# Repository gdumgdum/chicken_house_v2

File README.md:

# chicken_house_v2
Everything needed to automate a chicken house door controlled over RF by domotic softwares

#

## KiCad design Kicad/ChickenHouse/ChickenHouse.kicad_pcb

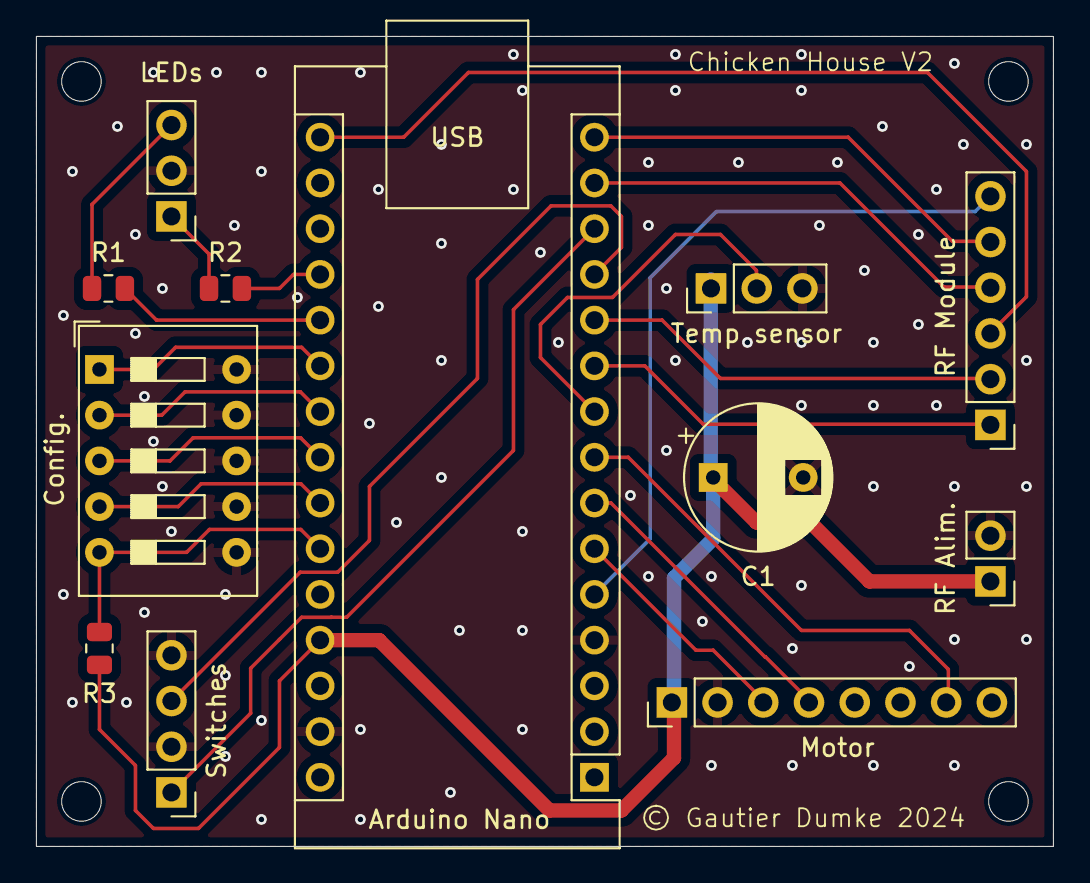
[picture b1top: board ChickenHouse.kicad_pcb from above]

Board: 2 copper layers, 56.5 x 45.0 mm, 12 parts (0 on the bottom side), 23 nets.

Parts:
Arduino Nano: Arduino_Nano_v3.x; Arduino_Nano
C1: 220µF/16V; CP_Radial_D8.0mm_P5.00mm
Config.: SW_DIP_x05; SW_DIP_SPSTx05_Slide_9.78x14.88mm_W7.62mm_P2.54mm
LEDs: LEDs; PinHeader_1x03_P2.54mm_Vertical
Motor: LM239D Shield; PinHeader_1x08_P2.54mm_Vertical
R1, R2, R3: 470; R_0805_2012Metric
RF Alim.: Conn_01x02; PinHeader_1x02_P2.54mm_Vertical
RF Module: Conn_01x06; PinHeader_1x06_P2.54mm_Vertical
Switches: Switches; PinHeader_1x04_P2.54mm_Vertical
Temp sensor: Temperature; PinHeader_1x03_P2.54mm_Vertical

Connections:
+5V: Arduino Nano.27 (+5V), C1.1, Motor.1, R3.1, RF Alim..1, Temp sensor.1
GND: Arduino Nano.4 (GND), Arduino Nano.29 (GND), C1.2, Config..6, Config..7, Config..8, Config..9, Config..10, LEDs.2, Motor.2, RF Alim..2, Switches.2, Switches.4, Temp sensor.3
unnamed: Arduino Nano.19 (A0), R2.2
unnamed: Arduino Nano.20 (A1), R1.2
unnamed: Arduino Nano.21 (A2), Config..1
unnamed: Arduino Nano.22 (A3), Config..2
unnamed: Arduino Nano.23 (A4), Config..3
unnamed: Arduino Nano.24 (A5), Config..4
unnamed: Arduino Nano.25 (A6), Config..5, R3.2
unnamed: Arduino Nano.5 (D2), RF Module.6
unnamed: Arduino Nano.6 (D3), Motor.3
unnamed: Arduino Nano.7 (D4), Motor.4
unnamed: Arduino Nano.8 (D5), Motor.7
unnamed: Arduino Nano.9 (D6), Temp sensor.2
unnamed: Arduino Nano.10 (D7), RF Module.1
unnamed: Arduino Nano.11 (D8), RF Module.2
unnamed: Arduino Nano.12 (D9), Switches.3
unnamed: Arduino Nano.13 (D10), Switches.1
unnamed: Arduino Nano.14 (D11), RF Module.4
unnamed: Arduino Nano.15 (D12), RF Module.5
unnamed: Arduino Nano.16 (D13), RF Module.3
unnamed: LEDs.1, R2.1
unnamed: LEDs.3, R1.1

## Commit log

2024-06-26 First and incomplete commit
2024-06-26 Fixes
2024-06-28 serial port list

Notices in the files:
Kicad/ChickenHouse/ChickenHouse.kicad_pcb:
© Gautier Dumke 2024
